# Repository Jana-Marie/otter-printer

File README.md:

# otter-printer

Controllerboard and FW for HP 302 cartridges

[Schematics](/printer-otter.pdf)

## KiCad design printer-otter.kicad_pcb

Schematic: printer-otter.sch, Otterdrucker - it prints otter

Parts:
C1, C2, C7: 1uF; C_0603_1608Metric
C3: 10µF; CP_Elec_4x3
C4, C5, C6, C18, C21, C22, C23, C24: 0.1μF; C_0603_1608Metric
C11: 1uF; C_0805_2012Metric
C20: 0.1μF; C_0805_2012Metric
D1: Power; LED_0603_1608Metric
D2: D_Schottky; D_SOD-123
D4: Status; LED_0603_1608Metric
J1: USB; USB-C 16Pin
J2: Printer; Generic_FPC_0.5mm_15pin
J4: Encoder; PinHeader_1x05_P2.54mm_Vertical
J5: UART; PinHeader_1x05_P2.54mm_Vertical
L1: 15µ; L_Taiyo-Yuden_MD-4040
Q1, Q3: Q_NMOS_GSD; SOT-23
Q2, Q4: Q_PMOS_GSD; SOT-23
R1, R3: 5k1; R_0603_1608Metric
R2, R5, R6, R7, R8, R9, R10, R11, R12, R13: 2k; R_0603_1608Metric
R4: 51k; R_0603_1608Metric
SW1: Down; SW_SPST_EVQP7C
U1: MT3608; SOT-23-6
U2: STM32F072C8Ux; QFN-48-1EP_7x7mm_P0.5mm_EP5.6x5.6mm
U3: AP2204R-3.3; SOT-89-3
U4: USBLC6-4SC6; SOT-23-6
U5: L78L09_SOT89; SOT-89-3
U6, U7: 4504; SOIC-16_3.9x9.9mm_P1.27mm

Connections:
9V: C18.1, C24.1, U5.1 (OUT), U7.16
16V: C3.1, C20.1, C22.1, D2.1, Q2.2, Q4.2, R4.1, R8.1, R13.1, U5.3 (IN), U6.16
+3V3: C2.1, C4.1, C5.1, C6.1, C7.1, C21.1, C23.1, J4.1, SW1.1, U2.1, U2.9, U2.24, U2.36, U2.48, U3.3 (VOUT), U4.5, U6.1, U7.1
BTN: R2.2, SW1.2, U2.44, U2.45
CSYNC: U2.31, U7.9
CSYNC_HV: J2.8, U7.10
D1: U2.2, U7.5
D1_HV: J2.4, U7.4
D2: U2.3, U7.7
D2_HV: J2.2, U7.6
D3: U2.4, U7.11
D3_HV: J2.9, U7.12
DCLK: U2.10, U6.14
DCLK_HV: J2.6, U6.15
ENCODER_A: J4.2, U2.30
ENCODER_B: J4.3, U2.29
F3: Q1.1, R6.1, U2.17
F3_HV: J2.1, Q2.3
F5: Q3.1, R11.1, U2.16
F5_HV: J2.7, Q4.3
GND: C1.2, C2.2, C3.2, C4.2, C5.2, C6.2, C7.2, C11.2, C18.2, C20.2, C21.2, C22.2, C23.2, C24.2, D1.1, D4.1, J1.A1, J1.B1, J1.S1, J2.15, J4.5, J5.5, Q1.2, Q3.2, R1.1, R2.1, R3.1, R5.2, R6.2, R11.2, U1.2, U2.8, U2.23, U2.35, U2.47, U2.49, U3.2 (GND), U4.2, U5.2 (GND), U6.8, U6.13, U7.8, U7.13
GPIO_ANALOG0: U2.39
GPIO_ANALOG1: U2.40
GPIO_ANALOG2: U2.41
INDEX: J4.4, U2.28
INT_IN: J5.2, U2.20
LED_Power: R9.1, U2.19
LED_Status: R10.1, U2.18
unnamed: D1.2, R9.2
unnamed: D2.2, L1.2, U1.1
unnamed: D4.2, R10.2
unnamed: J1.A5, R1.2
unnamed: J1.B5, R3.2
unnamed: Q1.3, R7.2
unnamed: Q2.1, R7.1, R8.2
unnamed: Q3.3, R12.2
unnamed: Q4.1, R12.1, R13.2
unnamed: R4.2, R5.1, U1.3
S1: U2.15, U6.7
S1_HV: J2.11, U6.6
S2: U2.13, U6.3
S2_HV: J2.13, U6.2
S3: U2.11, U6.9
S3_HV: J2.5, U6.10
S4: U2.14, U6.5
S4_HV: J2.12, U6.4
S5: U2.12, U6.11
S5_HV: J2.10, U6.12
SWCLK: U2.37
SWDIO: U2.34
UART_RX: J5.4, U2.22
UART_TX: J5.3, U2.21
USB_DN: J1.A7, J1.B7, U2.32, U4.1
USB_DP: J1.A6, J1.B6, U2.33, U4.6
VBUS: C1.1, C11.1, J1.A4, J1.B4, J5.1, L1.1, U1.4, U1.5, U3.1 (VIN)
nRST: U2.7

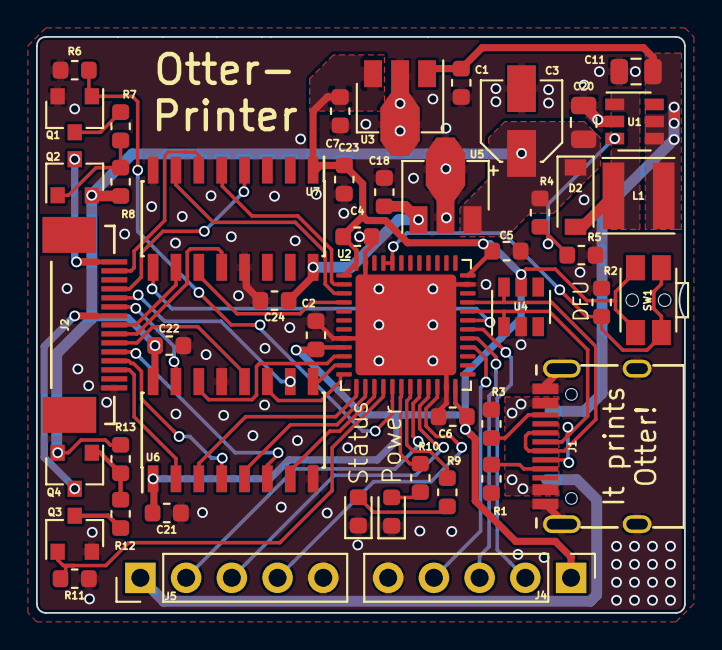
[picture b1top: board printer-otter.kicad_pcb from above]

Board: 2 copper layers, 36.0 x 32.0 mm, 47 parts (0 on the bottom side), 50 nets.

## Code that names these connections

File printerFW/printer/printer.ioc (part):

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Mcu.Name=STM32F072C(8-B)Ux
Mcu.Package=UFQFPN48
Mcu.UserName=STM32F072CBUx
PA0.GPIOParameters=GPIO_Label
PA0.GPIO_Label=DCLCK
PA0.Signal=GPIO_Output
PA1.GPIOParameters=GPIO_Label
PA1.GPIO_Label=S5
PA1.Signal=GPIO_Output
PA11.Mode=Device
PA11.Signal=USB_DM
PA12.Mode=Device
PA12.Signal=USB_DP
PA13.Mode=Serial_Wire
PA13.Signal=SYS_SWDIO
PA14.Mode=Serial_Wire
PA14.Signal=SYS_SWCLK
PA15.GPIOParameters=GPIO_Label
PA15.GPIO_Label=LED_STATUS
PA15.Signal=GPIO_Output
PA2.GPIOParameters=GPIO_Label
PA2.GPIO_Label=S2
PA2.Signal=GPIO_Output
PA3.GPIOParameters=GPIO_Label
PA3.GPIO_Label=S3
PA3.Signal=GPIO_Output
PA6.GPIOParameters=GPIO_Label
PA6.GPIO_Label=S4
PA6.Signal=GPIO_Output
PA7.GPIOParameters=GPIO_Label
PA7.GPIO_Label=S1
PA7.Signal=GPIO_Output
PA8.GPIOParameters=GPIO_Label
PA8.GPIO_Label=ENCODER_B
PA8.Signal=S_TIM1_CH1
PA9.GPIOParameters=GPIO_Label
PA9.GPIO_Label=ENCODER_A
PA9.Signal=S_TIM1_CH2
PB0.Signal=S_TIM3_CH3
PB1.Signal=S_TIM3_CH4
PB10.GPIOParameters=GPIO_Label
PB10.GPIO_Label=IN_TX
PB10.Mode=Asynchronous
PB10.Signal=USART3_TX
PB11.GPIOParameters=GPIO_Label
PB11.GPIO_Label=IN_RX
PB11.Mode=Asynchronous
PB11.Signal=USART3_RX
PB12.GPIOParameters=GPIO_Label
PB12.GPIO_Label=LED_STATUS
PB12.Signal=GPIO_Output
PB13.GPIOParameters=GPIO_Label
PB13.GPIO_Label=LED_POWER
PB13.Signal=GPIO_Output
PB15.GPIOParameters=GPIO_Label
PB15.GPIO_Label=INDEX
PB15.Signal=GPIO_Input
PB2.GPIOParameters=GPIO_Label
PB2.GPIO_Label=INT_IN
PB2.Signal=GPXTI2
PB3.GPIOParameters=GPIO_Label
PB3.GPIO_Label=ANALOG_INPUT3
PB3.Signal=GPIO_Analog
PB4.GPIOParameters=GPIO_Label
PB4.GPIO_Label=ANALOG_INPUT2
PB4.Signal=GPIO_Analog
PB5.GPIOParameters=GPIO_Label
PB5.GPIO_Label=ANALOG_INPUT1
PB5.Signal=GPIO_Analog
PB6.GPIOParameters=GPIO_Label
PB6.GPIO_Label=OLED_SCL
PB6.Mode=I2C
PB6.Signal=I2C1_SCL
PB7.GPIOParameters=GPIO_Label
PB7.GPIO_Label=OLED_SDA
PB7.Mode=I2C
PB7.Signal=I2C1_SDA
PB8.GPIOParameters=GPIO_Label
PB8.GPIO_Label=BUTTON
PB8.Signal=GPIO_Input
PB9.GPIOParameters=GPIO_Label
PB9.GPIO_Label=CSYNC
PB9.Signal=GPIO_Output
PC13.GPIOParameters=GPIO_Label
PC13.GPIO_Label=D1
PC13.Signal=GPIO_Output
PC14-OSC32_IN.GPIOParameters=GPIO_Label
PC14-OSC32_IN.GPIO_Label=D2
PC14-OSC32_IN.Signal=GPIO_Output
PC15-OSC32_OUT.GPIOParameters=GPIO_Label
PC15-OSC32_OUT.GPIO_Label=D3
PC15-OSC32_OUT.Signal=GPIO_Output
RCC.SYSCLKFreq_VALUE=48000000
RCC.SYSCLKSource=RCC_SYSCLKSOURCE_HSI48
board=custom

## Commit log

2019-02-25 added gitignore
2019-02-25 added files
2019-02-25 added FW
2019-02-25 updated libs
2019-02-26 added schematic pdf
2019-02-26 added connectors and board file
2019-02-26 renamed FW
2019-02-26 added printhead breakout board
2019-02-26 updated schematics file for breakout
2019-02-26 updated schematic, removed display and tag connect, routed board (80%)
2019-02-26 added image
2019-02-26 added README
2019-02-27 finalized layout
2019-02-27 schematic cleanup
2019-02-27 updated schematic pdf
2019-02-27 finalized board
2019-02-27 added images
2019-02-27 added gerber
2019-02-27 fixed FPC pinout
2019-02-27 regenerated gerber
2019-02-27 updated Images
2019-03-01 fixed USB-C plug and updated fiels
2019-03-15 updated FW
2019-03-15 file cleanup
2019-03-15 removed file
2019-03-17 added OPM
2019-03-17 updated files
2019-03-19 timer are working now
2019-03-20 code cleanup
2019-03-27 added logicdumps
2019-04-04 updated kicad files
2019-05-26 code finally works
2019-05-26 moved files
2019-05-26 gerber backup
2019-05-26 readded src files
2020-01-03 forgot to push
